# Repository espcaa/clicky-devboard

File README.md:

# Clicky devboard

## [[JOURNAL]](https://github.com/espcaa/clicky-devboard/blob/main/JOURNAL.md) - [[BOM]](https://github.com/espcaa/clicky-devboard/blob/main/kicad/production/bom.csv) - [[KICAD FILES]](https://github.com/espcaa/clicky-devboard/tree/main/kicad)

This is a devboard based on the RP2350 chip (the rp2040's successor) with three mechanical switches, with every gpio exposed on pin headers + extras like 3v3 and vbus. It was entirely designed in Kicad and everything is open source! 4 layer board that can be manufactured with normal jlcpcb tolerances.\
\

## Main components

- RP2350
- 3x Cherry MX switches
- Recommended abracon crystal & inductors
- AP63203WU-7 for the 5v to 3v3 conversion
- 1x23 pin headers
- W25Q64JVSSIQ_C179171 chip for the flash (64mb)
- a usb-c connector

## Features

- clicky
- ~~might work~~ works!
- open source

## Schematic/PCB

 \

you can download everything in the [kicad/ folder](https://github.com/espcaa/clicky-devboard/tree/main/kicad)

## Notes

- there's a resistor missing for the usb-c, so it only works in one orientation :(

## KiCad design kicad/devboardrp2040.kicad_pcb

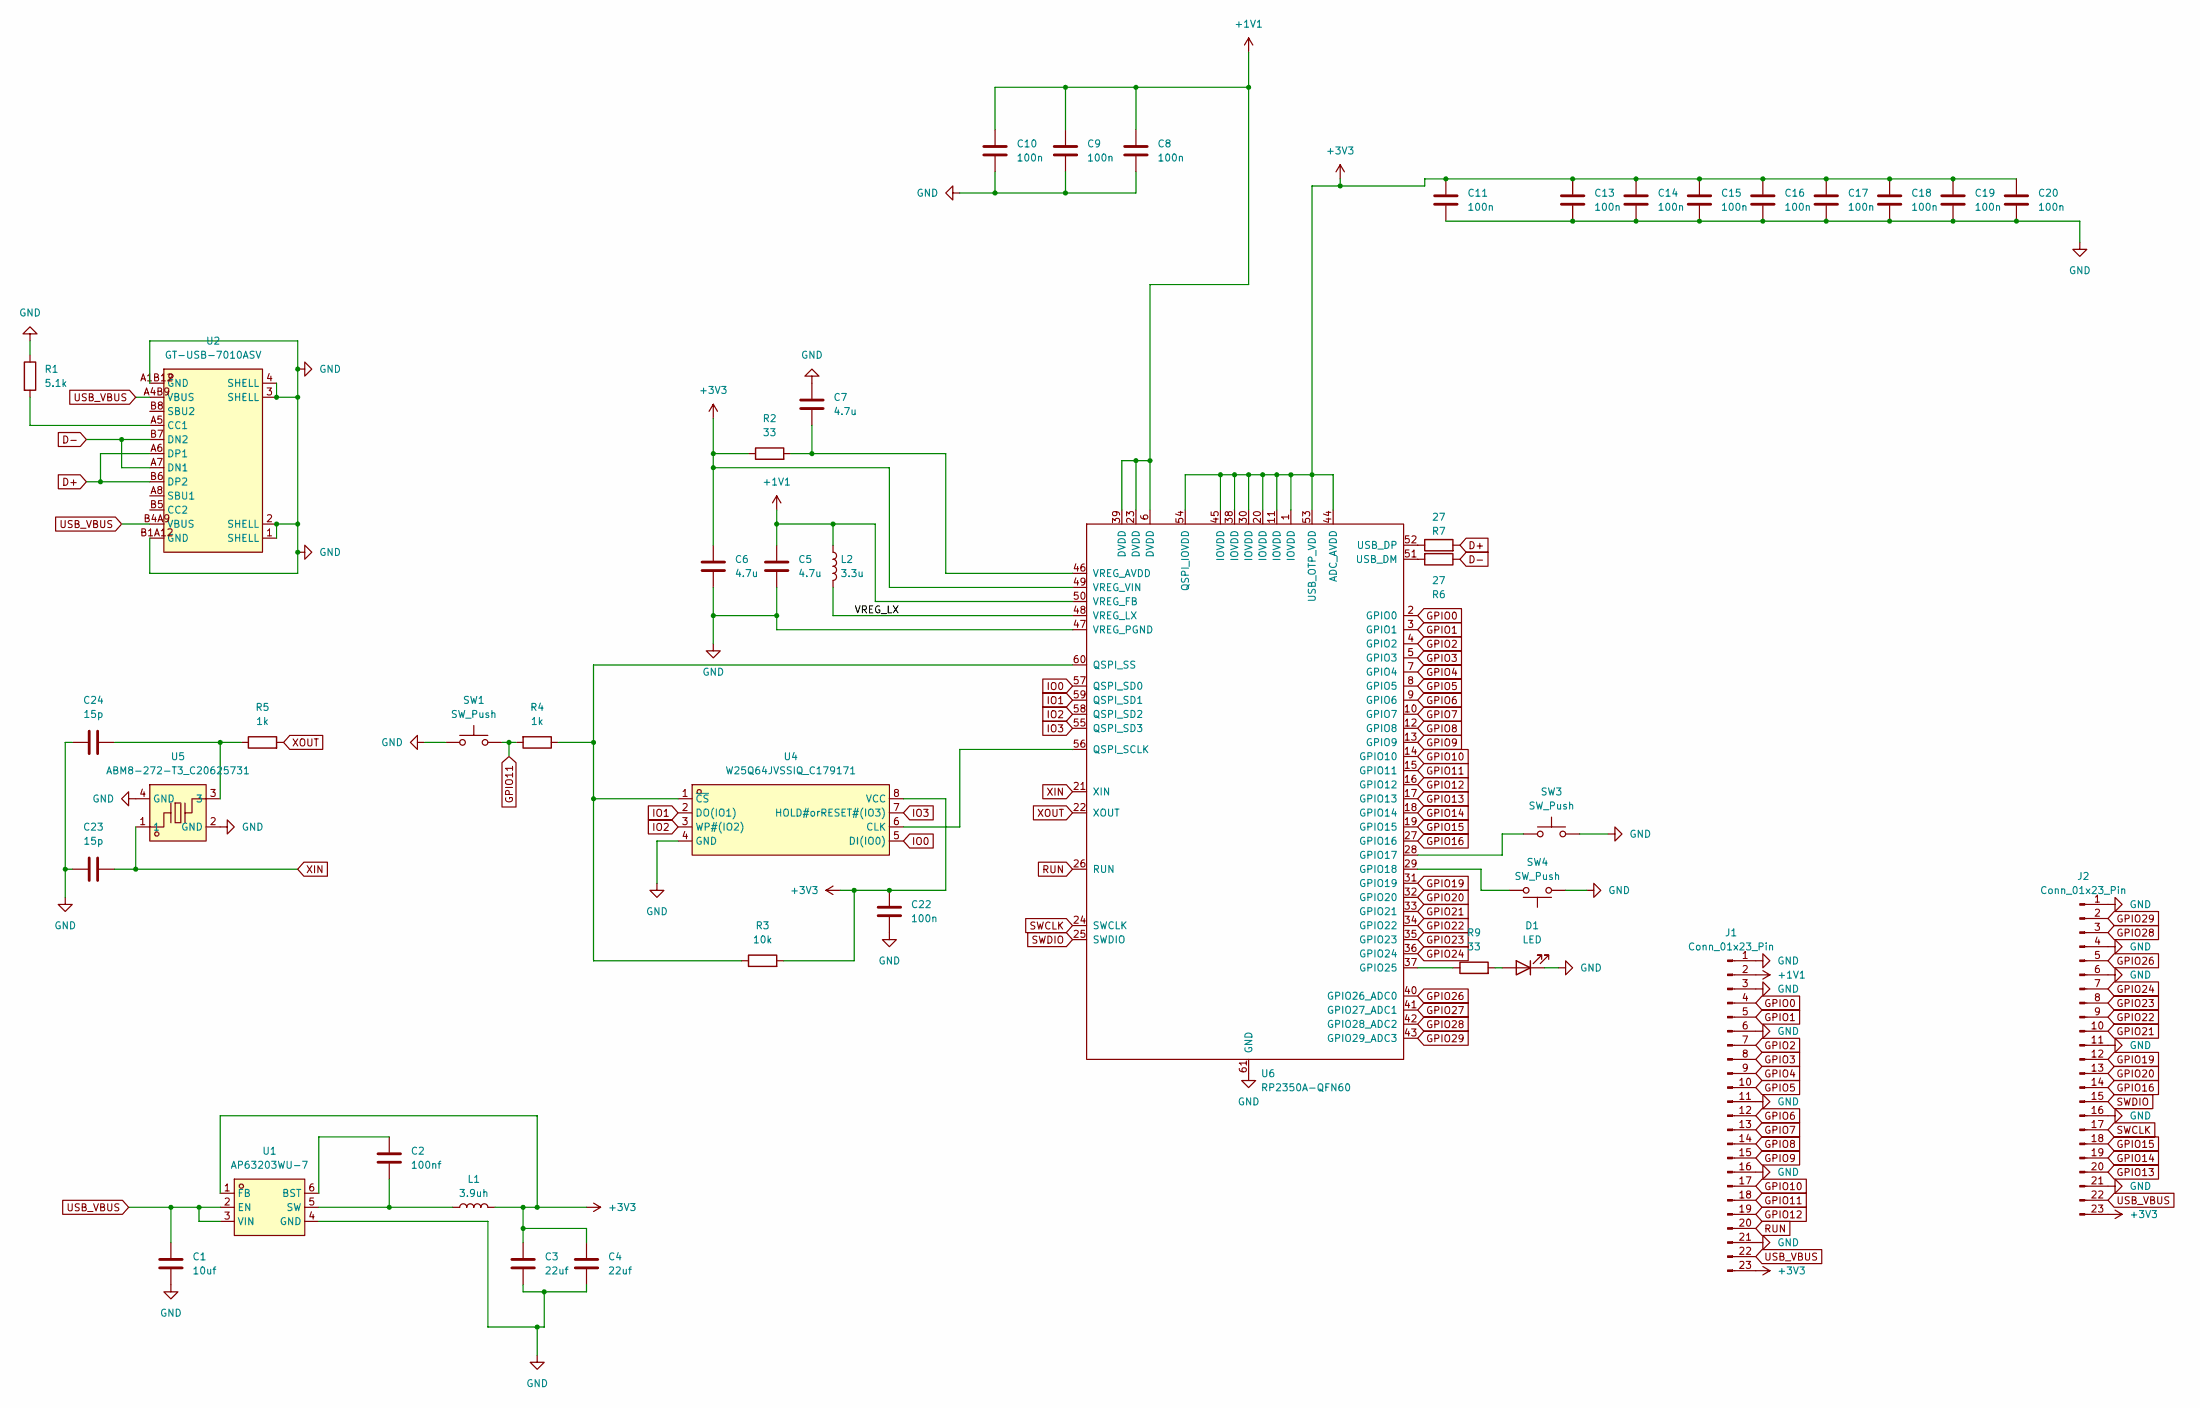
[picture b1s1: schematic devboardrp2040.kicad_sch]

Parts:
C1: 10uf; C_0805_2012Metric
C2: 100nf; C_0402_1005Metric
C3, C4: 22uf; C_0603_1608Metric
C5, C6, C7: 4.7u; C_0402_1005Metric_small_pads
C8, C9, C10, C11, C13, C14, C15, C16, C17, C18, C19, C20, C22: 100n; C_0402_1005Metric
C23, C24: 15p; C_0402_1005Metric
D1: LED; LED_0402_1005Metric
J1, J2: Conn_01x23_Pin; PinHeader_1x23_P2.54mm_Vertical
L1: 3.9uh; L_1210_3225Metric
L2: 3.3u; 0603-special
R1: 5.1k; R_0402_1005Metric
R2, R9: 33; R_0402_1005Metric
R3: 10k; R_0402_1005Metric
R4, R5: 1k; R_0402_1005Metric
R6, R7: 27; R_0402_1005Metric
SW1, SW3, SW4: SW_Push; SW_Cherry_MX_1.00u_Plate
U1: AP63203WU-7; TSOT-26_L2.9-W1.6-P0.95-LS2.8-BL; LCSC Part C780769
U2: GT-USB-7010ASV; USB-C-SMD_G-SWITCH_GT-USB-7010ASV; LCSC Part C2988369
U4: W25Q64JVSSIQ_C179171; SOIC-8_L5.3-W5.3-P1.27-LS8.0-BL; LCSC Part C179171
U5: ABM8-272-T3_C20625731; CRYSTAL-SMD_4P-L3.2-W2.5-BL; LCSC Part C20625731
U6: RP2350A-QFN60; QFN-60-1EP_7x7mm_P0.4mm_EP3.4x3.4mm

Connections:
+1V1: C5.1, C8.1, C9.1, C10.1, J1.2, L2.1, U6.6 (DVDD), U6.23 (DVDD), U6.39 (DVDD), U6.50 (VREG_FB)
+3V3: C3.1, C4.1, C6.1, C11.1, C13.1, C14.1, C15.1, C16.1, C17.1, C18.1, C19.1, C20.1, C22.1, J1.23, J2.23, L1.2, R2.1, R3.2, U1.1 (FB), U4.8 (VCC), U6.1 (IOVDD), U6.11 (IOVDD), U6.20 (IOVDD), U6.30 (IOVDD), U6.38 (IOVDD), U6.44 (ADC_AVDD), U6.45 (IOVDD), U6.49 (VREG_VIN), U6.53 (USB_OTP_VDD), U6.54 (QSPI_IOVDD)
/VREG_LX: L2.2, U6.48 (VREG_LX)
D+: R7.2, U2.A6 (DP1), U2.B6 (DP2)
D-: R6.1, U2.A7 (DN1), U2.B7 (DN2)
GND: C1.2, C3.2, C4.2, C5.2, C6.2, C7.1, C8.2, C9.2, C10.2, C11.2, C13.2, C14.2, C15.2, C16.2, C17.2, C18.2, C19.2, C20.2, C22.2, C23.1, C24.1, D1.1 (K), J1.1, J1.3, J1.6, J1.11, J1.16, J1.21, J2.1, J2.4, J2.6, J2.11, J2.16, J2.21, R1.1, SW1.1, SW3.2, SW4.1, U1.4 (GND), U2.1 (SHELL), U2.2 (SHELL), U2.3 (SHELL), U2.4 (SHELL), U2.A1B12 (GND), U2.B1A12 (GND), U4.4 (GND), U5.2 (GND), U5.4 (GND), U6.47 (VREG_PGND), U6.61 (GND)
GPIO0: J1.4, U6.2 (GPIO0)
GPIO1: J1.5, U6.3 (GPIO1)
GPIO2: J1.7, U6.4 (GPIO2)
GPIO3: J1.8, U6.5 (GPIO3)
GPIO4: J1.9, U6.7 (GPIO4)
GPIO5: J1.10, U6.8 (GPIO5)
GPIO6: J1.12, U6.9 (GPIO6)
GPIO7: J1.13, U6.10 (GPIO7)
GPIO8: J1.14, U6.12 (GPIO8)
GPIO9: J1.15, U6.13 (GPIO9)
GPIO10: J1.17, U6.14 (GPIO10)
GPIO11: J1.18, R4.2, SW1.2, U6.15 (GPIO11)
GPIO12: J1.19, U6.16 (GPIO12)
GPIO13: J2.20, U6.17 (GPIO13)
GPIO14: J2.19, U6.18 (GPIO14)
GPIO15: J2.18, U6.19 (GPIO15)
GPIO16: J2.14, U6.27 (GPIO16)
GPIO19: J2.12, U6.31 (GPIO19)
GPIO20: J2.13, U6.32 (GPIO20)
GPIO21: J2.10, U6.33 (GPIO21)
GPIO22: J2.9, U6.34 (GPIO22)
GPIO23: J2.8, U6.35 (GPIO23)
GPIO24: J2.7, U6.36 (GPIO24)
GPIO26: J2.5, U6.40 (GPIO26_ADC0)
GPIO27: U6.41 (GPIO27_ADC1)
GPIO28: J2.3, U6.42 (GPIO28_ADC2)
GPIO29: J2.2, U6.43 (GPIO29_ADC3)
IO0: U4.5 (DI(IO0)), U6.57 (QSPI_SD0)
IO1: U4.2 (DO(IO1)), U6.59 (QSPI_SD1)
IO2: U4.3 (WP#(IO2)), U6.58 (QSPI_SD2)
IO3: U4.7 (HOLD#orRESET#(IO3)), U6.55 (QSPI_SD3)
unnamed: C24.2, R5.1, U5.3
unnamed: D1.2 (A), R9.2
unnamed: C2.1, U1.6 (BST)
unnamed: C2.2, L1.1, U1.5 (SW)
unnamed: R1.2, U2.A5 (CC1)
unnamed: U4.6 (CLK), U6.56 (QSPI_SCLK)
unnamed: R3.1, R4.1, U4.1 (~CS), U6.60 (QSPI_SS)
unnamed: SW3.1, U6.28 (GPIO17)
unnamed: SW4.2, U6.29 (GPIO18)
unnamed: R9.1, U6.37 (GPIO25)
unnamed: R6.2, U6.51 (USB_DM)
unnamed: R7.1, U6.52 (USB_DP)
unnamed: C7.2, R2.2, U6.46 (VREG_AVDD)
RUN: J1.20, U6.26 (RUN)
SWCLK: J2.17, U6.24 (SWCLK)
SWDIO: J2.15, U6.25 (SWDIO)
USB_VBUS: C1.1, J1.22, J2.22, U1.2 (EN), U1.3 (VIN), U2.A4B9 (VBUS), U2.B4A9 (VBUS)
XIN: C23.2, U5.1, U6.21 (XIN)
XOUT: R5.2, U6.22 (XOUT)

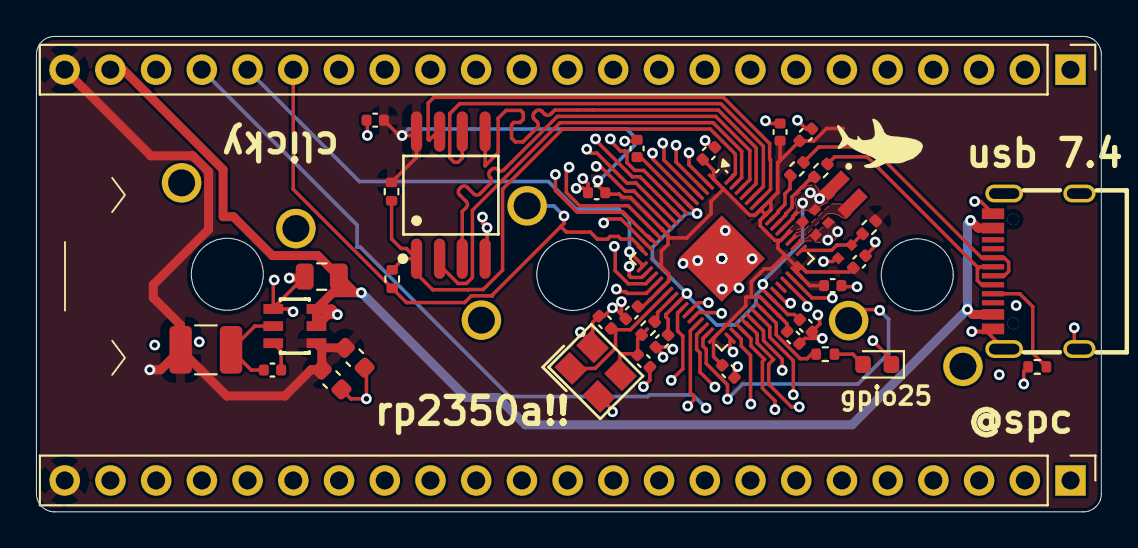
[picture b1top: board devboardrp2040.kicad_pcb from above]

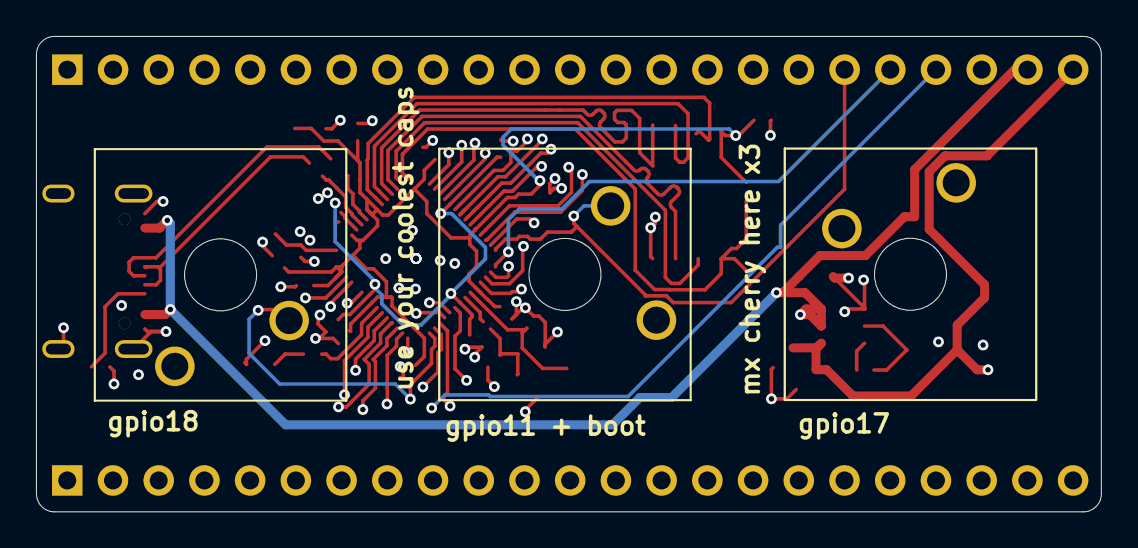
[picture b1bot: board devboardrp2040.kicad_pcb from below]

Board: 4 copper layers, 59.2 x 26.4 mm, 43 parts (3 on the bottom side), 55 nets.

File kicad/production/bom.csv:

Designator,Footprint,Quantity,Value,LCSC Part #
C1,0805,1,10uf,
"C10, C11, C13, C14, C15, C16, C17, C18, C19, C20, C22, C8, C9",0402,13,100n,
C2,0402,1,100nf,
"C23, C24",0402,2,15p,
"C3, C4",0603,2,22uf,
"C5, C6, C7",0402,3,4.7u,
D1,0603,1,LED,
"J1, J2",PinHeader_1x23_P2.54mm_Vertical,2,Conn_01x23_Pin,
L1,1210,1,3.9uh,
L2,0603-special,1,3.3u,C42411119
R1,0402,1,5.1k,
"R2, R9",0402,2,33,
R3,0402,1,10k,
"R4, R5",0402,2,1k,
"R6, R7",0402,2,27,
"SW1, SW3, SW4",SW_Cherry_MX_1.00u_Plate,3,SW_Push,
U1,TSOT-26_L2.9-W1.6-P0.95-LS2.8-BL,1,AP63203WU-7,C780769
U2,USB-C-SMD_G-SWITCH_GT-USB-7010ASV,1,GT-USB-7010ASV,C2988369
U4,SOIC-8_L5.3-W5.3-P1.27-LS8.0-BL,1,W25Q64JVSSIQ_C179171,C179171
U5,CRYSTAL-SMD_4P-L3.2-W2.5-BL,1,ABM8-272-T3_C20625731,C20625731
U6,QFN-60-1EP_7x7mm_P0.4mm_EP3.4x3.4mm,1,RP2350A-QFN60,

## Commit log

2025-08-02 first commit!
2025-08-02 updated the kicad files
2025-08-02 hiii
2025-08-06 removed macos eww
2025-08-07 FINISHED KAUHdiodu
2025-08-08 readme
2025-08-08 kicad updates
2025-08-08 silkscreen!!!
2026-01-29 fixed the confusing naming
